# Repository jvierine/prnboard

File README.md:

# PRNboard

A standalone GNSS-timed PRN ionosonde exciter, intended to replace the transmit USRP and `tx_uhd.py` in [ionosonde](https://github.com/jvierine/ionosonde).

- **0.5–30 MHz**, uploaded binary phase code, **10–1000 µs chips** (default **30 µs**).
- **Continuous phase-continuous LFM**, typically **100 or 500 kHz/s**, using the AD9954 hardware ramp engine.
- Up to **1000 frequencies in user-defined order**, timed sweeps or single-frequency operation.
- GNSS PPS and disciplined **10 MHz TCXO**. **No qualified timing/frequency lock → no transmission.**
- **Wi-Fi and USB** configuration; stored programs run without a computer or internet.
- SMA exciter output; optional **separate protected, cooled 10 W PA**, with harmonic filtering and final 50 MHz LPF.
- Future telemetry and seven independently coded exciter outputs.

**Target: $50–100 per assembled exciter board**, using common parts with sustainable sourcing. Antenna, enclosure, adapter, cables, tax, freight, engineering, and PA are excluded. Revision B components total about **$77**, using a conservative $45 DDS allowance. Allow roughly **$95–115 assembled** in small batches; this is an estimate, not a fabrication quote.

**Current draft:** RP2040 timing/USB controller, ESP32-S3 Wi-Fi, AD9954 DDS (200 MHz, internal ×20 PLL), and stocked MAX-M10S GNSS. PRN and LFM register-level reference simulations pass; physical hardware remains untested. Any suitable dual-frequency raw-data receiver may replace the single-frequency fallback when availability and cost allow; TEC is optional.

**Status:** editable KiCad circuit and **unrouted placement study**, plus a tested host program compiler and end-to-end reference simulation. **Not ready to order.** Routing, firmware, sourcing and RF/timing validation remain. No fabrication order has been placed.

Current 95 × 85 mm placement draft, top view. Copper routing is unfinished; the 10 W PA is separate.

[End-to-end simulation and results](docs/end-to-end.md) · [Revision B and remaining work](docs/revision-b.md) · [LFM results](docs/lfm.md) · [Sourcing](docs/sourcing.md) · [Requirements](docs/requirements.md)

Open `hardware/prnboard.kicad_pro` in KiCad 10.

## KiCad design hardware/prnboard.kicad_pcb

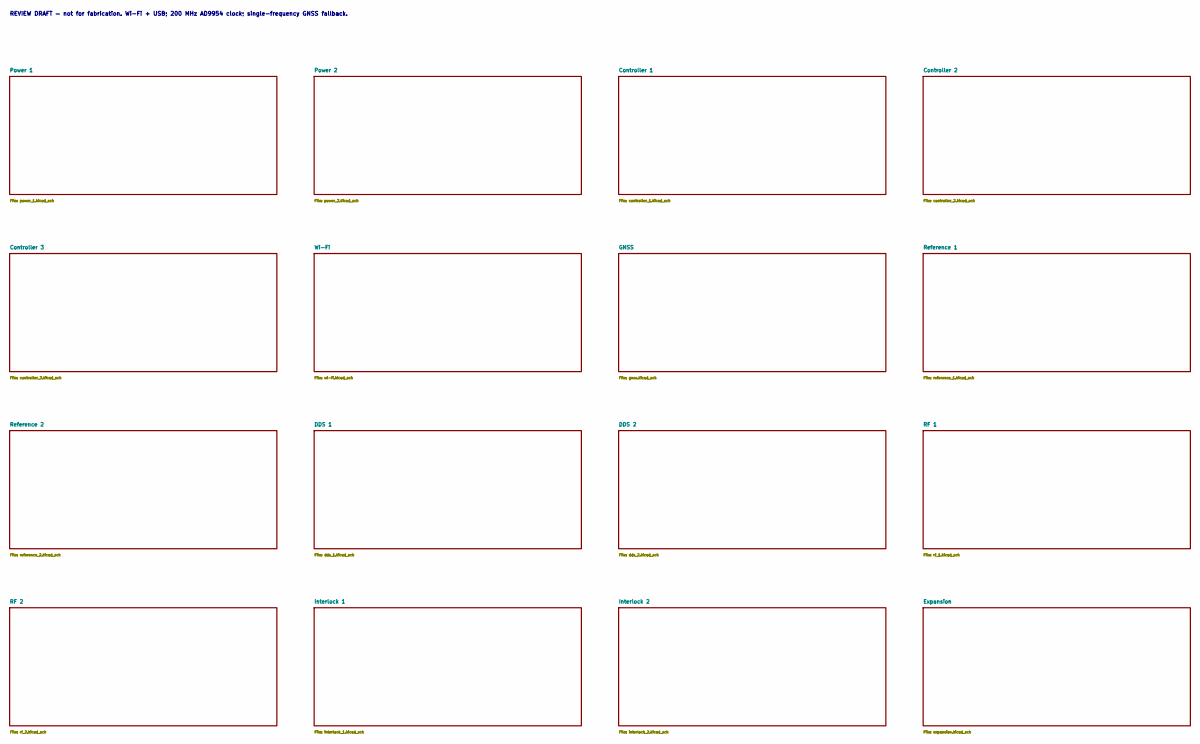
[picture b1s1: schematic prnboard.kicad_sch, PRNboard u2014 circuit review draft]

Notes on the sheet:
REVIEW DRAFT — not for fabrication. Wi-Fi + USB; 200 MHz AD9954 clock; single-frequency GNSS fallback.

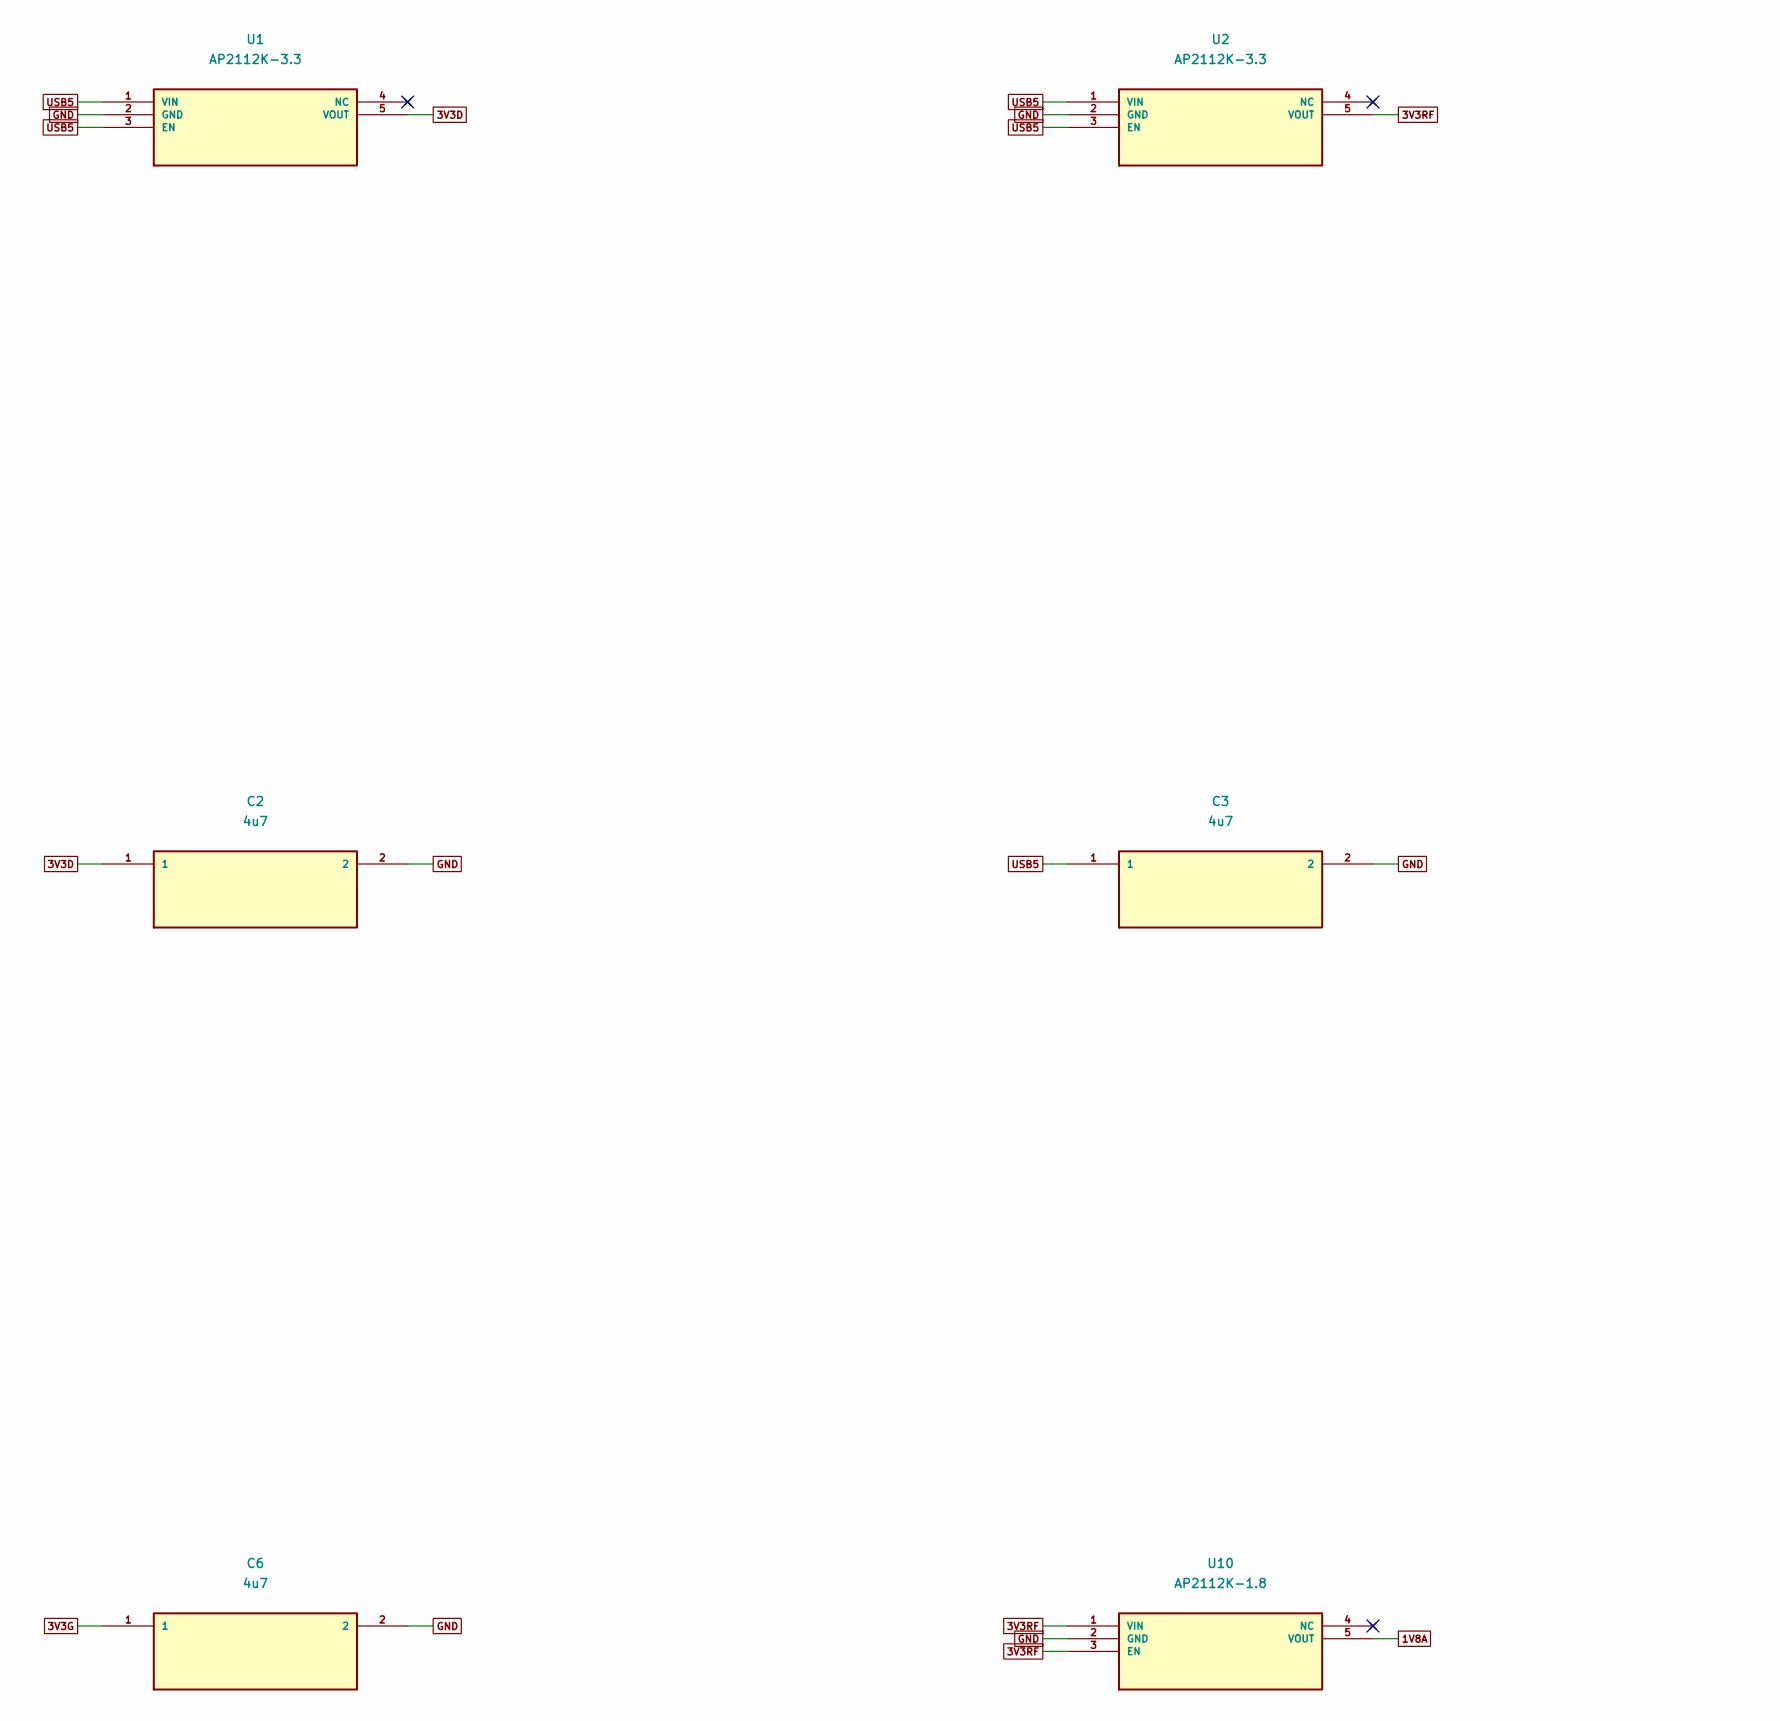
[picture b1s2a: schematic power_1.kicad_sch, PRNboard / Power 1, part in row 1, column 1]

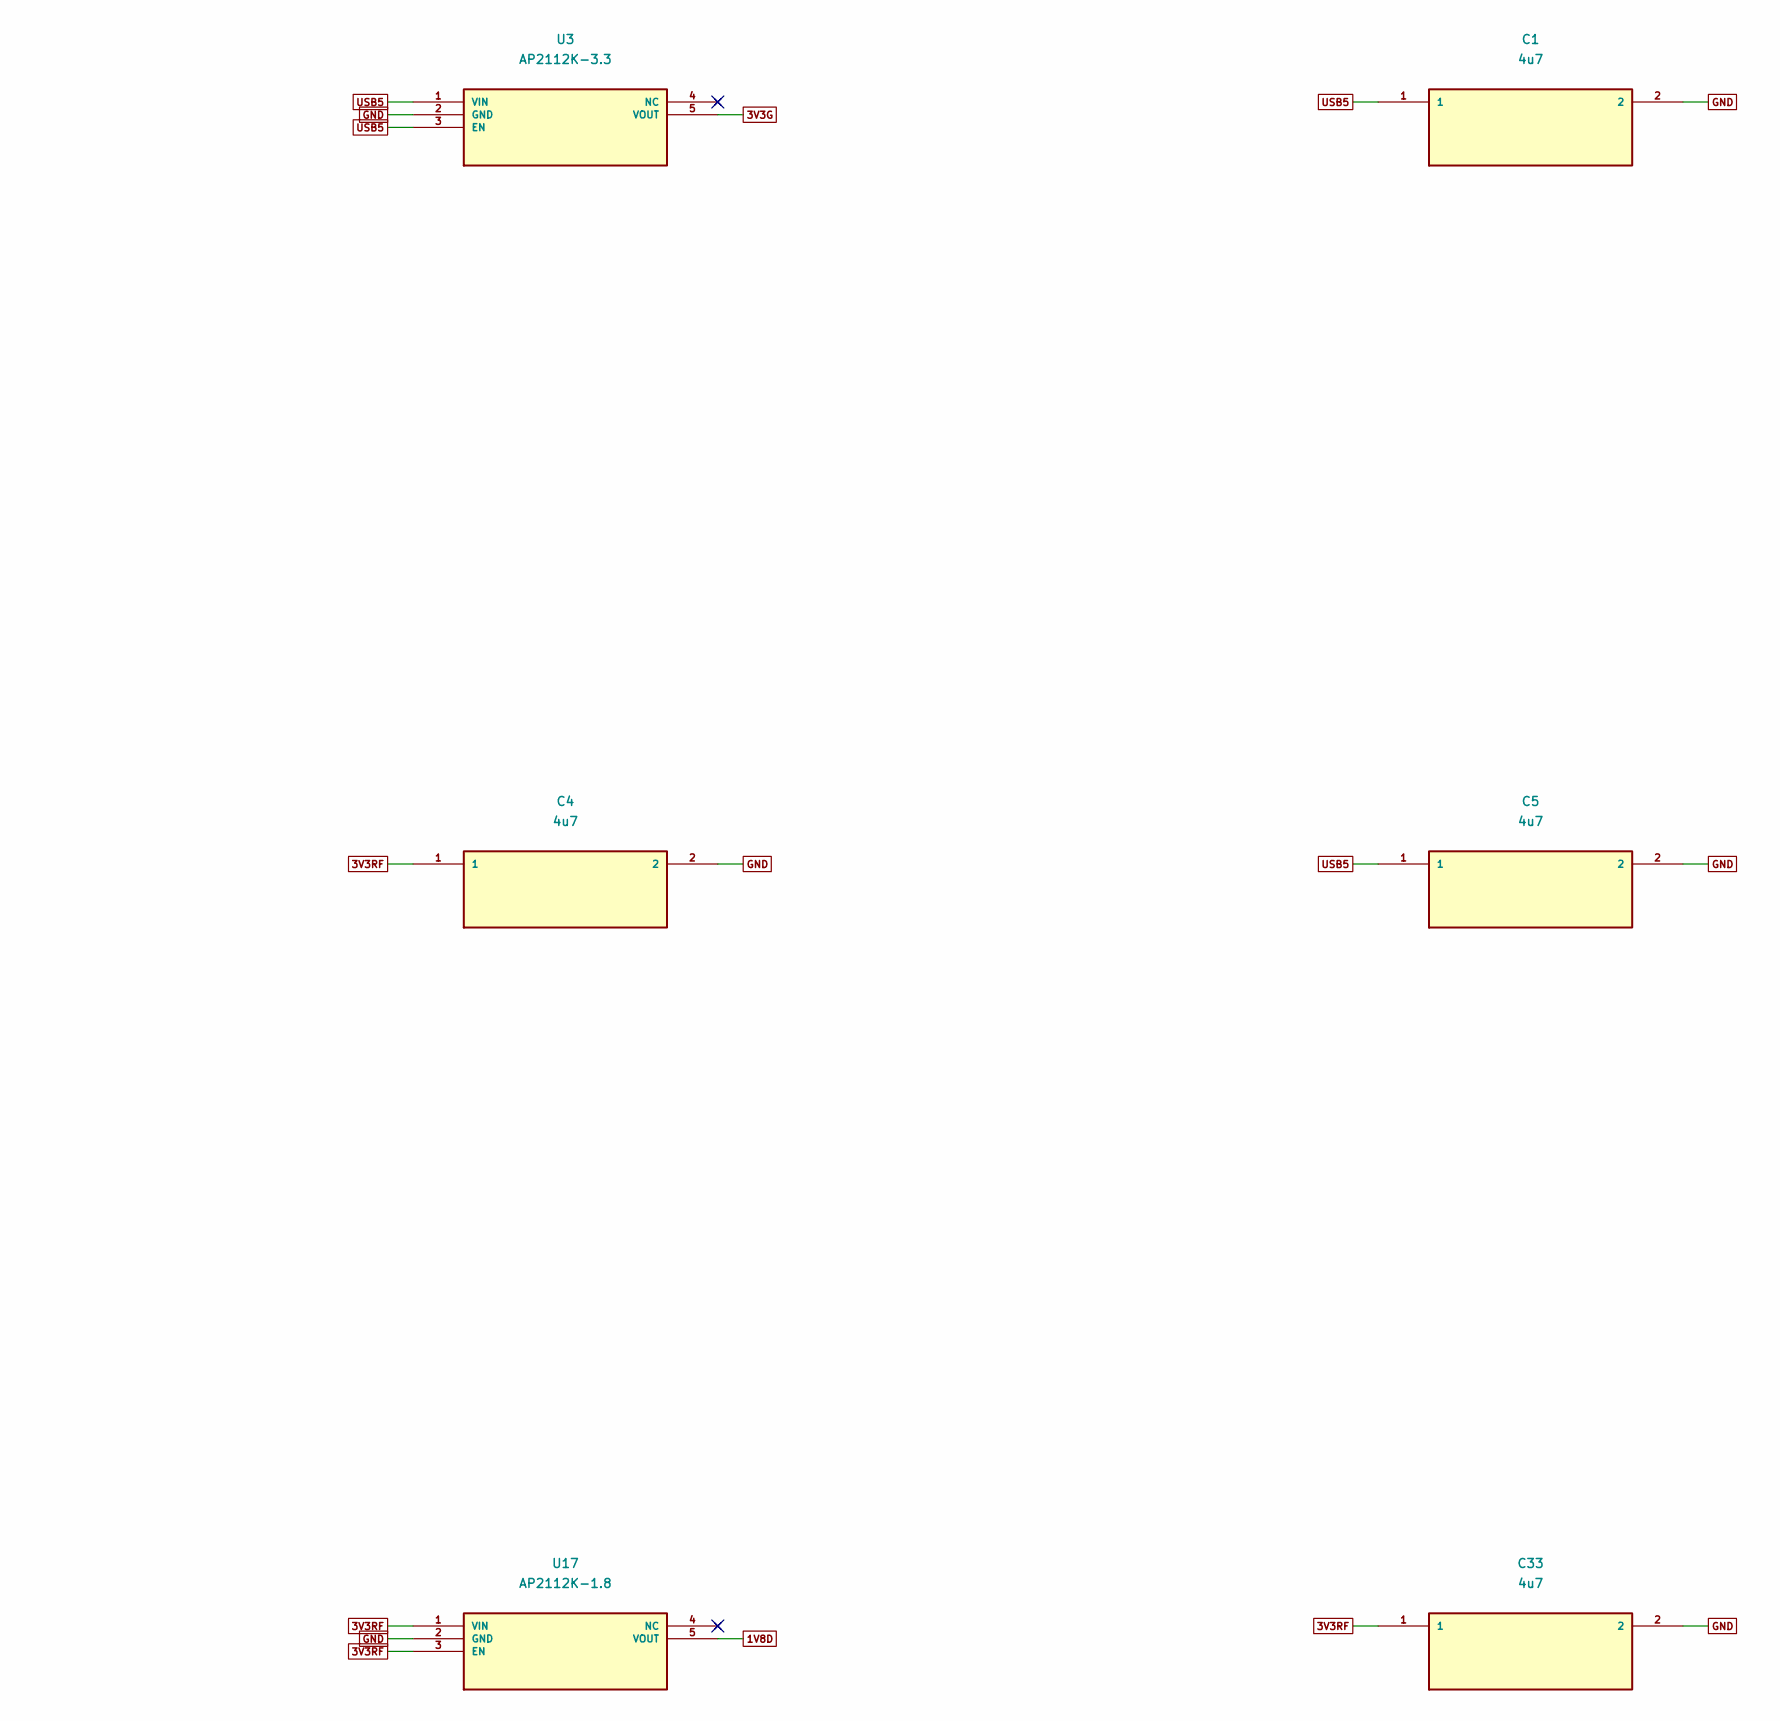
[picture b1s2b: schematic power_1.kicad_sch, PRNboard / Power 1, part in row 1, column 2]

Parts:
C1: 4u7; C1; MPN SELECT_IN_BOM
C2: 4u7; C2; MPN SELECT_IN_BOM
C3: 4u7; C3; MPN SELECT_IN_BOM
C4: 4u7; C4; MPN SELECT_IN_BOM
C5: 4u7; C5; MPN SELECT_IN_BOM
C6: 4u7; C6; MPN SELECT_IN_BOM
C33: 4u7; C33; MPN SELECT_IN_BOM
U1: AP2112K-3.3; U1; MPN AP2112K-3.3TRG1; LCSC C51118
U2: AP2112K-3.3; U2; MPN AP2112K-3.3TRG1; LCSC C51118
U3: AP2112K-3.3; U3; MPN AP2112K-3.3TRG1; LCSC C51118
U10: AP2112K-1.8; U10; MPN AP2112K-1.8TRG1
U17: AP2112K-1.8; U17; MPN AP2112K-1.8TRG1

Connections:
1V8A: U10.5 (VOUT); also elsewhere on the board
1V8D: U17.5 (VOUT); also elsewhere on the board
3V3D: C2.1, U1.5 (VOUT); also elsewhere on the board
3V3G: C6.1, U3.5 (VOUT); also elsewhere on the board
3V3RF: C4.1, C33.1, U2.5 (VOUT), U10.1 (VIN), U10.3 (EN), U17.1 (VIN), U17.3 (EN); also elsewhere on the board
GND: C1.2, C2.2, C3.2, C4.2, C5.2, C6.2, C33.2, U1.2 (GND), U2.2 (GND), U3.2 (GND), U10.2 (GND), U17.2 (GND); also elsewhere on the board
USB5: C1.1, C3.1, C5.1, U1.1 (VIN), U1.3 (EN), U2.1 (VIN), U2.3 (EN), U3.1 (VIN), U3.3 (EN); also elsewhere on the board

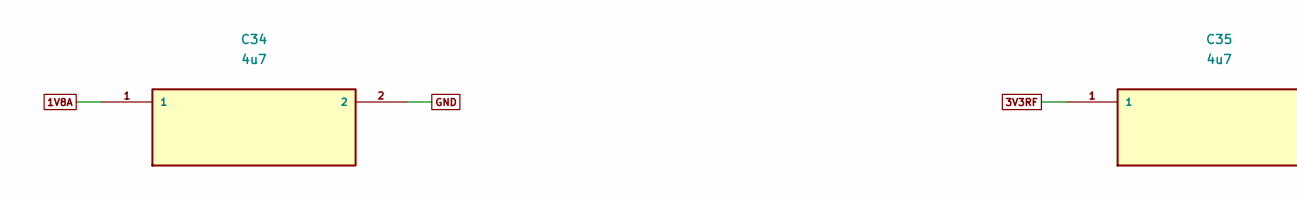
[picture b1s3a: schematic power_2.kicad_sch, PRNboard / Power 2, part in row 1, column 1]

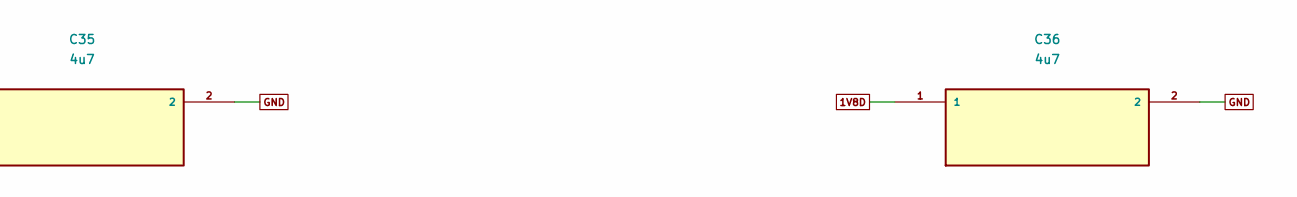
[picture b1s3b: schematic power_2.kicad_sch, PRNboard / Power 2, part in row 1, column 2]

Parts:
C34: 4u7; C34; MPN SELECT_IN_BOM
C35: 4u7; C35; MPN SELECT_IN_BOM
C36: 4u7; C36; MPN SELECT_IN_BOM

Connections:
1V8A: C34.1; also elsewhere on the board
1V8D: C36.1; also elsewhere on the board
3V3RF: C35.1; also elsewhere on the board
GND: C34.2, C35.2, C36.2; also elsewhere on the board

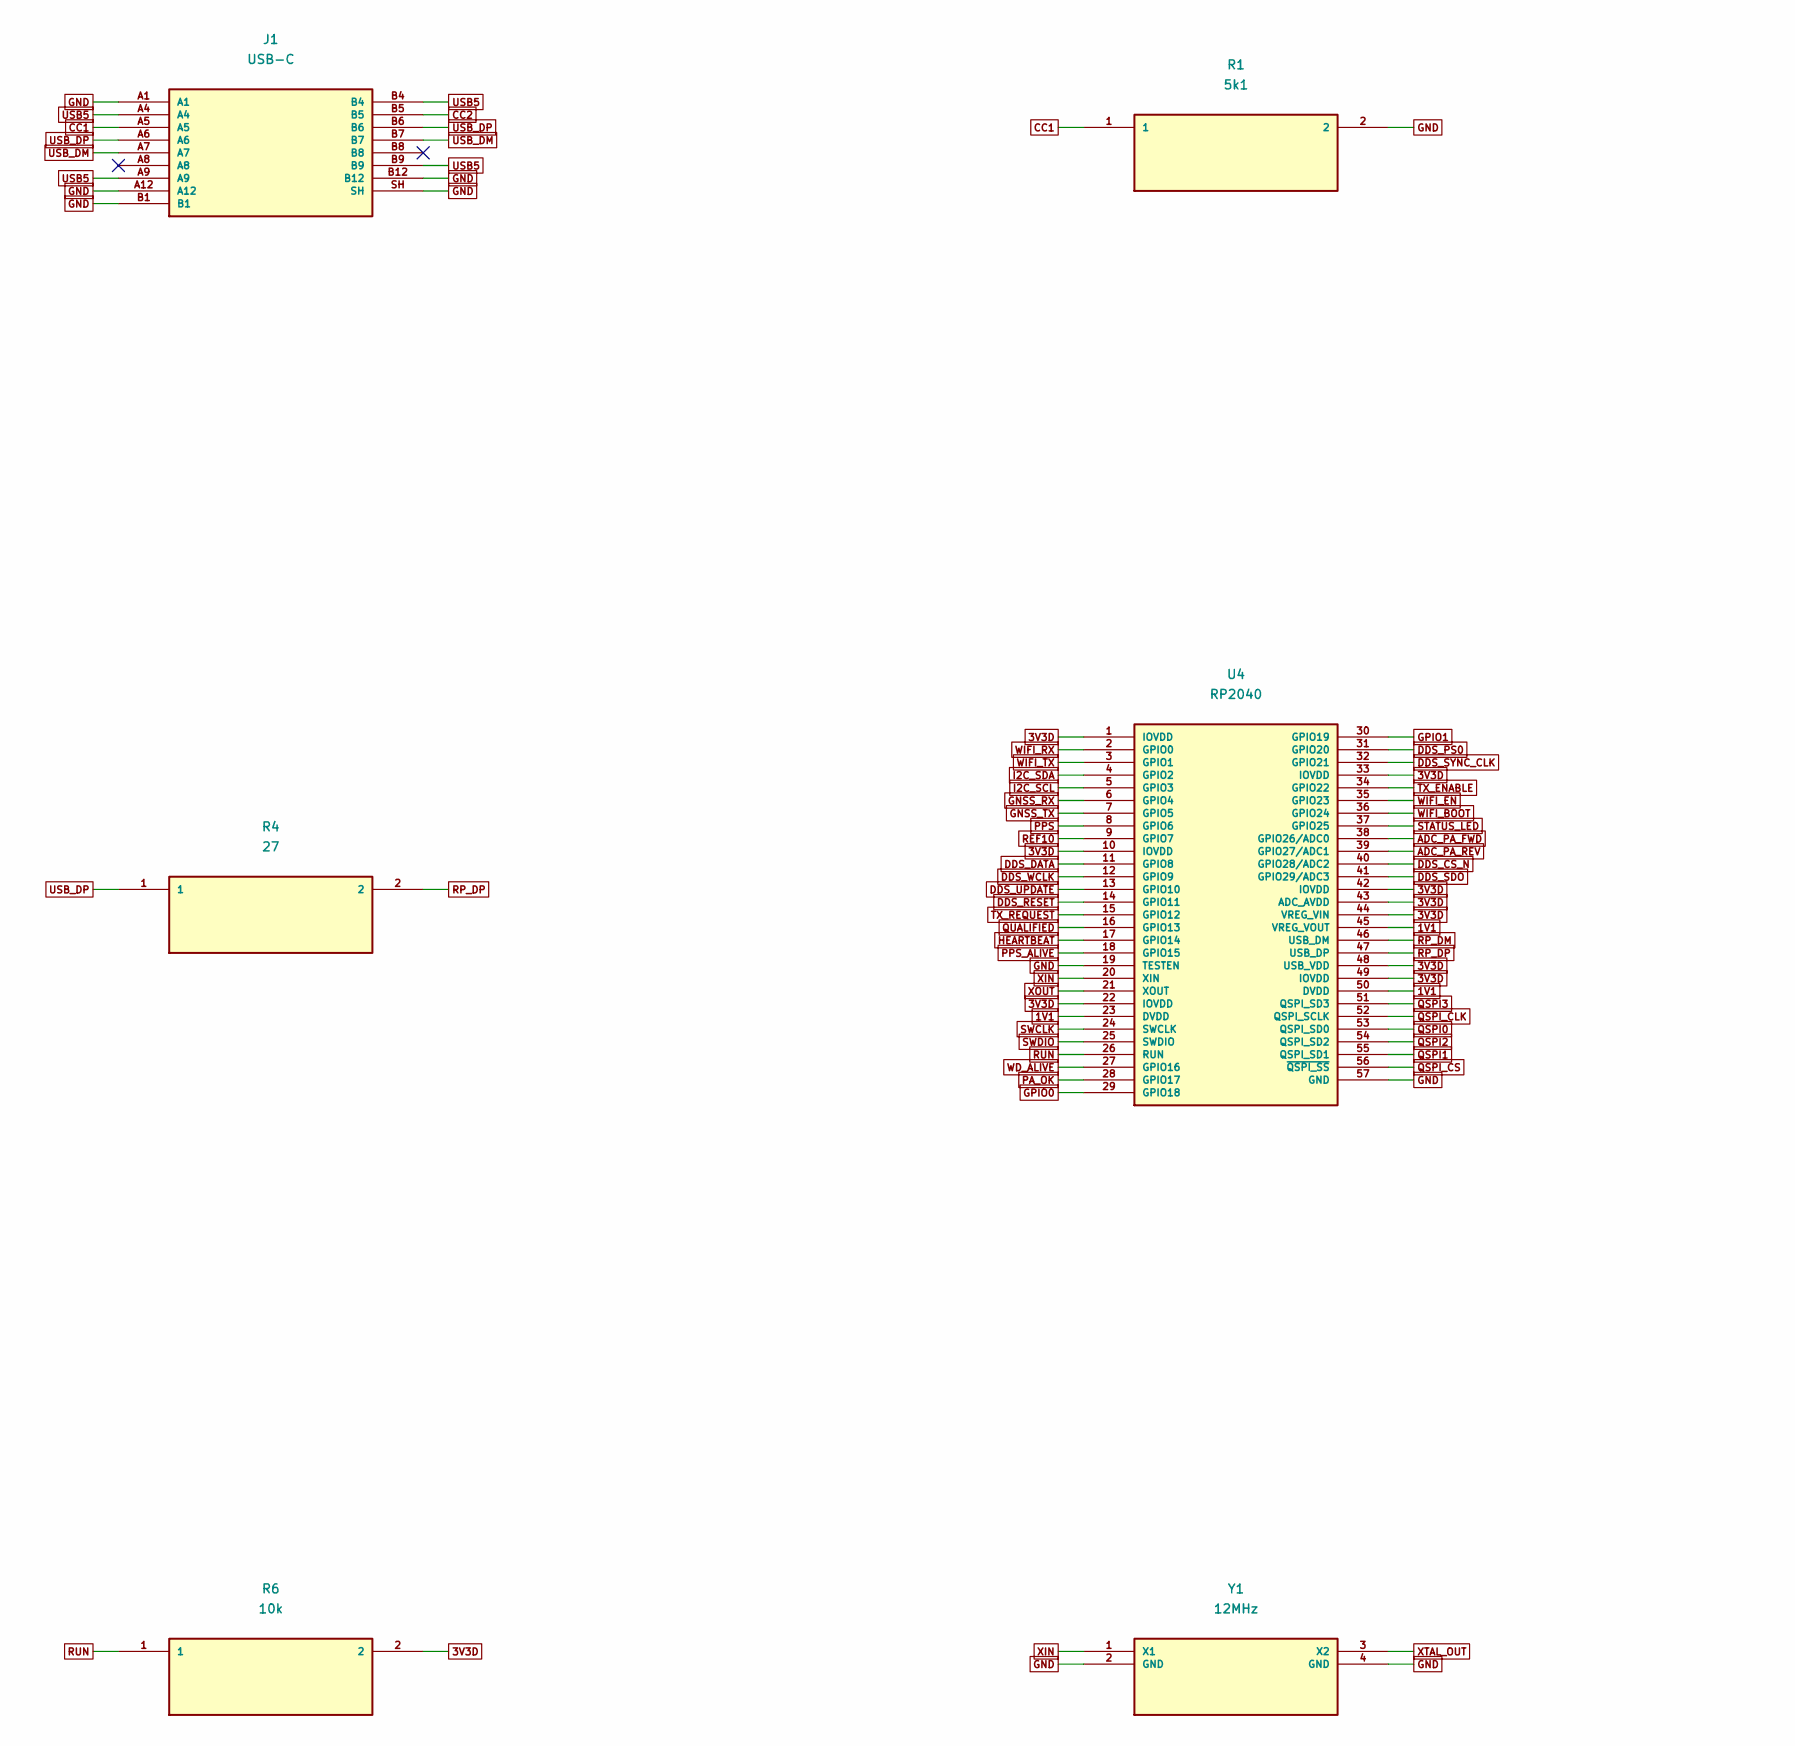
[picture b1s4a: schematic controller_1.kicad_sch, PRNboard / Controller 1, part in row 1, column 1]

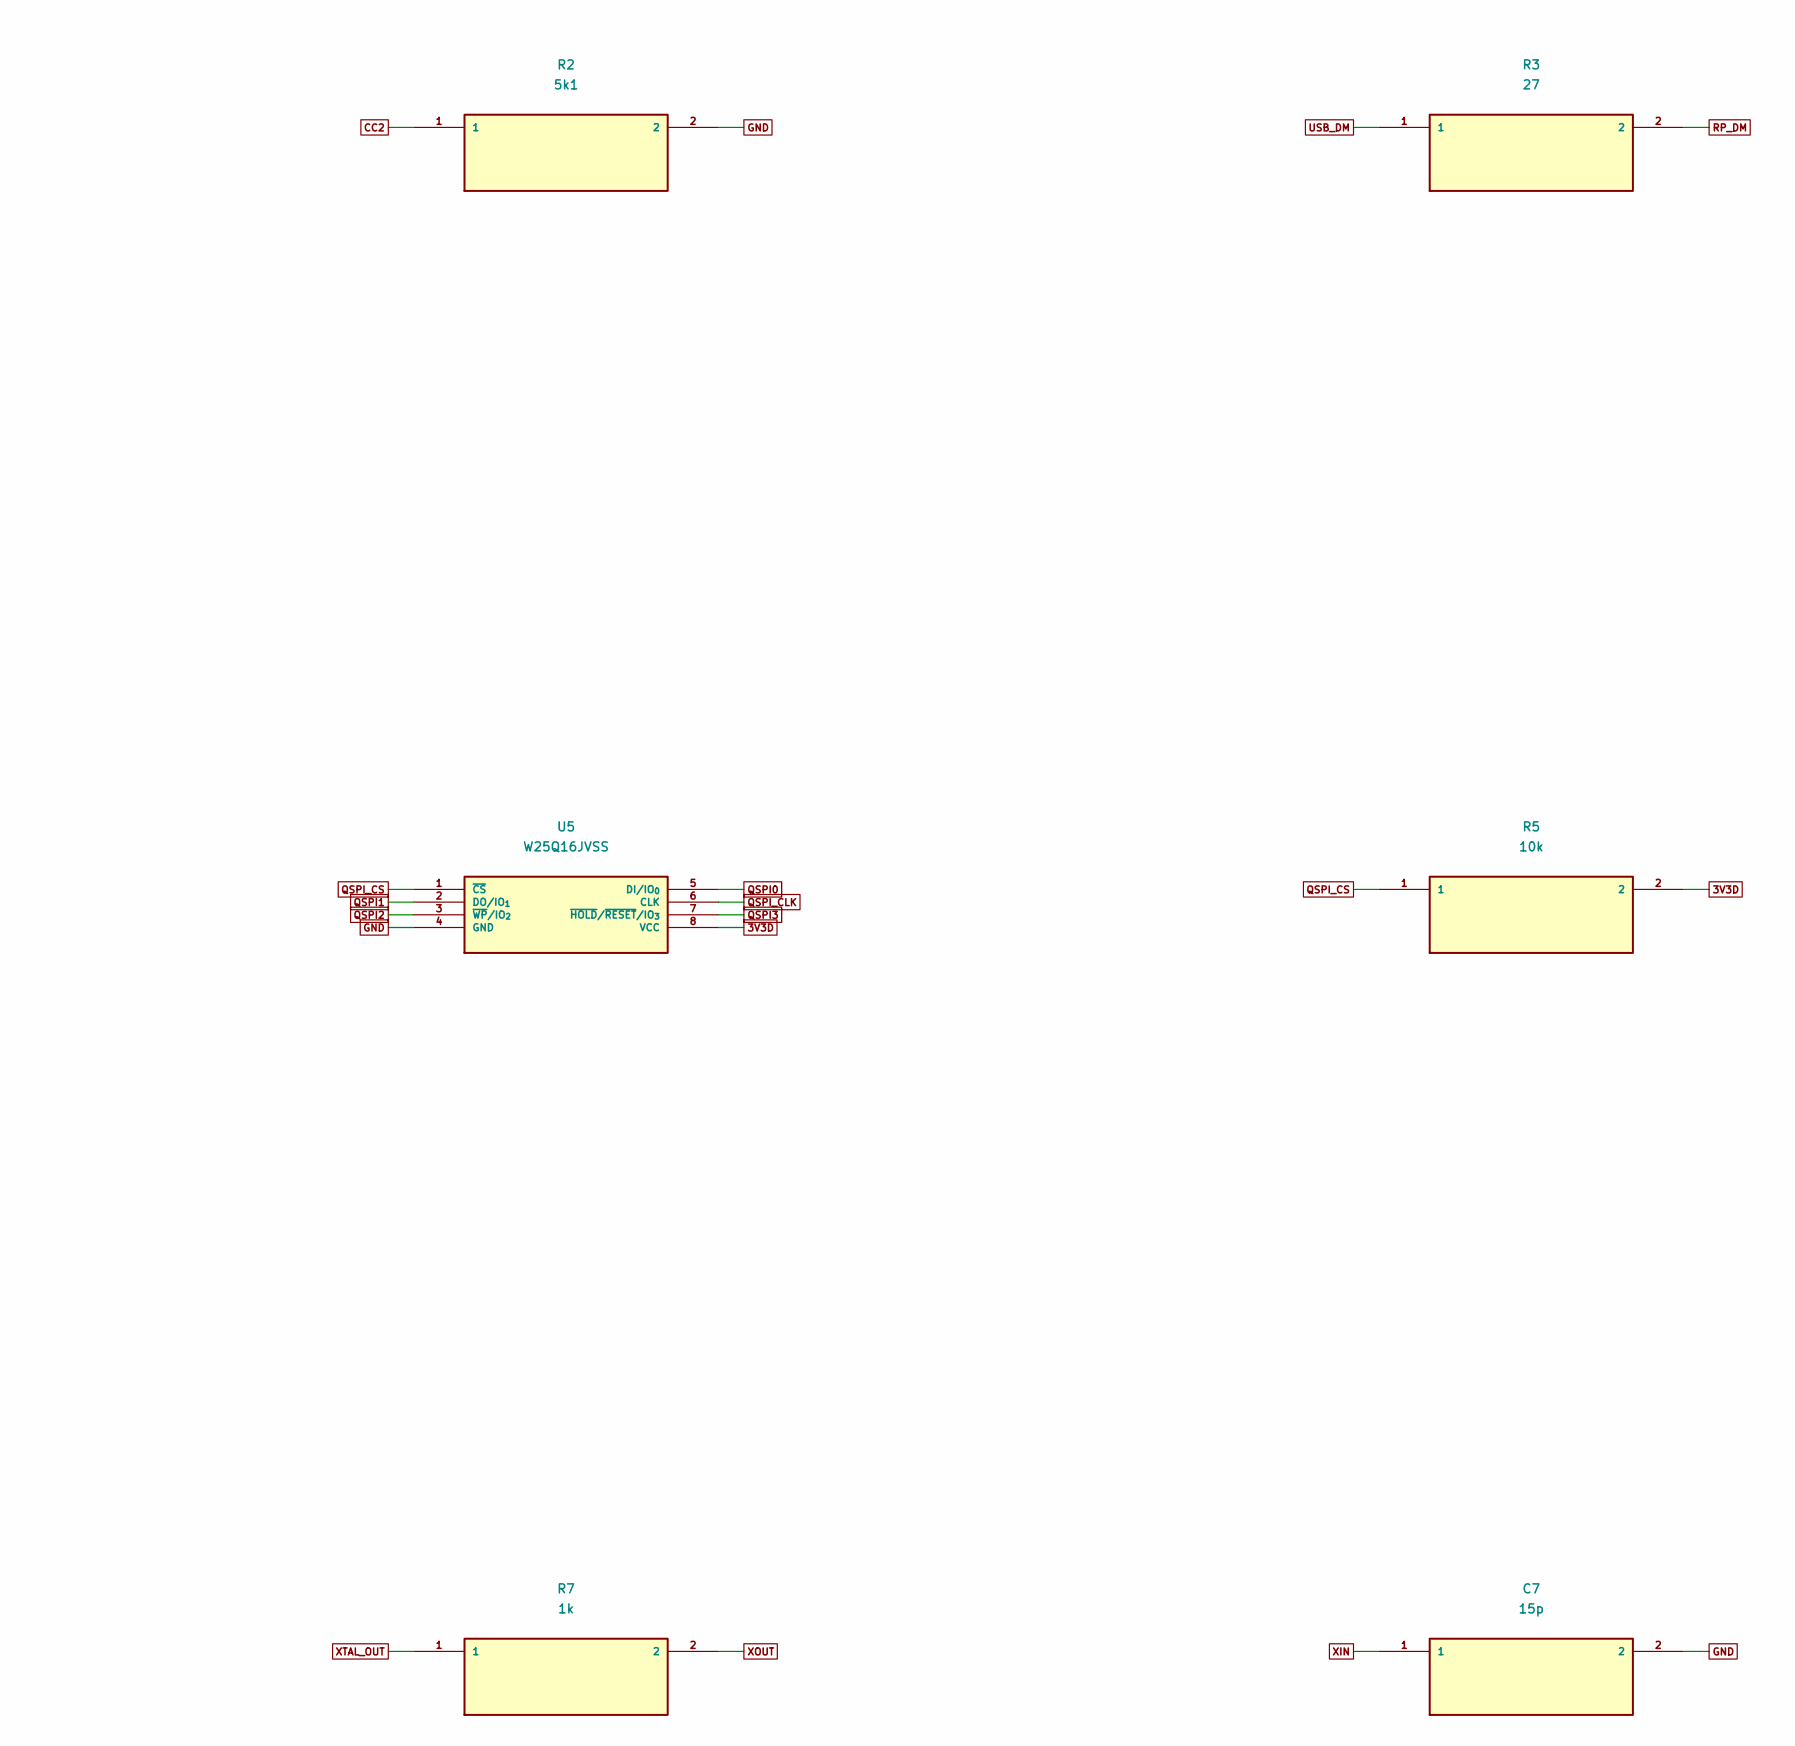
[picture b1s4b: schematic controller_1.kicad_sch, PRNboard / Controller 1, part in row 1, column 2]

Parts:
C7: 15p; C7; MPN SELECT_IN_BOM
J1: USB-C; J1; MPN TYPE-C-31-M-12; LCSC C165948
R1: 5k1; R1; MPN SELECT_IN_BOM
R2: 5k1; R2; MPN SELECT_IN_BOM
R3: 27; R3; MPN SELECT_IN_BOM
R4: 27; R4; MPN SELECT_IN_BOM
R5: 10k; R5; MPN SELECT_IN_BOM
R6: 10k; R6; MPN SELECT_IN_BOM
R7: 1k; R7; MPN SELECT_IN_BOM
U4: RP2040; U4; MPN RP2040; LCSC C2040
U5: W25Q16JVSS; U5; MPN W25Q16JVSS
Y1: 12MHz; Y1; MPN ABM8-272-T3

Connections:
1V1: U4.23 (DVDD), U4.45 (VREG_VOUT), U4.50 (DVDD); also elsewhere on the board
3V3D: R5.2, R6.2, U4.1 (IOVDD), U4.10 (IOVDD), U4.22 (IOVDD), U4.33 (IOVDD), U4.42 (IOVDD), U4.43 (ADC_AVDD), U4.44 (VREG_VIN), U4.48 (USB_VDD), U4.49 (IOVDD), U5.8 (VCC); also elsewhere on the board
ADC_PA_FWD: U4.38 (GPIO26/ADC0); also elsewhere on the board
ADC_PA_REV: U4.39 (GPIO27/ADC1); also elsewhere on the board
CC1: J1.A5, R1.1
CC2: J1.B5, R2.1
DDS_CS_N: U4.40 (GPIO28/ADC2); also elsewhere on the board
DDS_DATA: U4.11 (GPIO8); also elsewhere on the board
DDS_PS0: U4.31 (GPIO20); also elsewhere on the board
DDS_RESET: U4.14 (GPIO11); also elsewhere on the board
DDS_SDO: U4.41 (GPIO29/ADC3); also elsewhere on the board
DDS_SYNC_CLK: U4.32 (GPIO21); also elsewhere on the board
DDS_UPDATE: U4.13 (GPIO10); also elsewhere on the board
DDS_WCLK: U4.12 (GPIO9); also elsewhere on the board
GND: C7.2, J1.A1, J1.A12, J1.B1, J1.B12, J1.SH, R1.2, R2.2, U4.19 (TESTEN), U4.57 (GND), U5.4 (GND), Y1.2 (GND), Y1.4 (GND); also elsewhere on the board
GNSS_RX: U4.6 (GPIO4); also elsewhere on the board
GNSS_TX: U4.7 (GPIO5); also elsewhere on the board
GPIO0: U4.29 (GPIO18); also elsewhere on the board
GPIO1: U4.30 (GPIO19); also elsewhere on the board
HEARTBEAT: U4.17 (GPIO14); also elsewhere on the board
I2C_SCL: U4.5 (GPIO3); also elsewhere on the board
I2C_SDA: U4.4 (GPIO2); also elsewhere on the board
PA_OK: U4.28 (GPIO17); also elsewhere on the board
PPS: U4.8 (GPIO6); also elsewhere on the board
PPS_ALIVE: U4.18 (GPIO15); also elsewhere on the board
QSPI0: U4.53 (QSPI_SD0), U5.5 (DI/IO_{0})
QSPI1: U4.55 (QSPI_SD1), U5.2 (DO/IO_{1})
QSPI2: U4.54 (QSPI_SD2), U5.3 (~WP/IO_{2})
QSPI3: U4.51 (QSPI_SD3), U5.7 (~HOLD/~RESET/IO_{3})
QSPI_CLK: U4.52 (QSPI_SCLK), U5.6 (CLK)
QSPI_CS: R5.1, U4.56 (~QSPI_SS), U5.1 (~CS); also elsewhere on the board
QUALIFIED: U4.16 (GPIO13); also elsewhere on the board
REF10: U4.9 (GPIO7); also elsewhere on the board
RP_DM: R3.2, U4.46 (USB_DM)
RP_DP: R4.2, U4.47 (USB_DP)
RUN: R6.1, U4.26 (RUN); also elsewhere on the board
STATUS_LED: U4.37 (GPIO25); also elsewhere on the board
SWCLK: U4.24 (SWCLK); also elsewhere on the board
SWDIO: U4.25 (SWDIO); also elsewhere on the board
TX_ENABLE: U4.34 (GPIO22); also elsewhere on the board
TX_REQUEST: U4.15 (GPIO12); also elsewhere on the board
USB5: J1.A4, J1.A9, J1.B4, J1.B9; also elsewhere on the board
USB_DM: J1.A7, J1.B7, R3.1; also elsewhere on the board
USB_DP: J1.A6, J1.B6, R4.1; also elsewhere on the board
WD_ALIVE: U4.27 (GPIO16); also elsewhere on the board
WIFI_BOOT: U4.36 (GPIO24); also elsewhere on the board
WIFI_EN: U4.35 (GPIO23); also elsewhere on the board
WIFI_RX: U4.2 (GPIO0); also elsewhere on the board
WIFI_TX: U4.3 (GPIO1); also elsewhere on the board
XIN: C7.1, U4.20 (XIN), Y1.1 (X1)
XOUT: R7.2, U4.21 (XOUT)
XTAL_OUT: R7.1, Y1.3 (X2); also elsewhere on the board

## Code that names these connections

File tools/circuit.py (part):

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def cap(ref,net,x,y,section='Power',value='100n'):return passive(ref,value,net,'GND',x,y,section,'C')
# Regulator blocks: ESP radio current peaks isolated from GNSS/clock/DDS rails.
for ref,rail,x,y,enable in [('U1','3V3D',18,22,'USB5'),('U2','3V3RF',64,24,'USB5'),('U3','3V3G',78,25,'USB5')]:
 add(ref,'AP2112K-3.3', 'Power',x,y,pins=['VIN','GND','EN','NC','VOUT'],nets={'1':'USB5','2':'GND','3':enable,'5':rail},fp='Package_TO_SOT_SMD:SOT-23-5',mpn='AP2112K-3.3TRG1',cost=.18,lcsc='C51118')
for i,(rail,x,y) in enumerate([('USB5',14,22),('3V3D',22,22),('USB5',60,24),('3V3RF',68,24),('USB5',74,25),('3V3G',82,25)],1):cap('C'+str(i),rail,x,y,value='4u7')
# USB-C receptacle, both CC pull-downs. Connector pad map must be confirmed with exact supplier drawing.
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add('U4','RP2040','Controller',28,34,'MCU_RaspberryPi','RP2040',rp,mpn='RP2040',cost=.9,lcsc='C2040')
add('U5','W25Q16JVSS','Controller',16,35,'Memory_Flash','W25Q16JVSS',{'1':'QSPI_CS','2':'QSPI1','3':'QSPI2','4':'GND','5':'QSPI0','6':'QSPI_CLK','7':'QSPI3','8':'3V3D'},cost=.35)
passive('R5','10k','QSPI_CS','3V3D',16,30,'Controller');passive('R6','10k','RUN','3V3D',25,24,'Controller')
add('Y1','12MHz','Controller',28,46,pins=['X1','GND','X2','GND'],nets={'1':'XIN','2':'GND','3':'XTAL_OUT','4':'GND'},fp='Crystal:Crystal_SMD_3225-4Pin_3.2x2.5mm',mpn='ABM8-272-T3',cost=.2)
passive('R7','1k','XTAL_OUT','XOUT',32,46,'Controller');cap('C7','XIN',24,46,'Controller','15p');cap('C8','XTAL_OUT',28,50,'Controller','15p')
for i,(rail,x,y) in enumerate([('3V3D',25,29),('3V3D',31,29),('3V3D',33,34),('3V3D',31,39),('3V3D',25,39),('1V1',23,34),('1V1',29,41),('3V3D',16,39)],9):cap('C'+str(i),rail,x,y,'Controller')
cap('C17','1V1',23,38,'Controller','1u');cap('C18','RUN',25,21,'Controller')
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g={'1':'GND','2':'GNSS_TX','3':'GNSS_RX','4':'PPS','6':'3V3G','7':'3V3G','8':'3V3G','10':'GND','11':'GNSS_RF','12':'GND'}
add('U7','MAX-M10S-00B','GNSS',78,12,'RF_GPS','MAX-M10S',g,mpn='MAX-M10S-00B',cost=10.5062,lcsc='C4153167',note='VIO_SEL and TIMEPULSE/SAFEBOOT left unpulled. Single-frequency: no dual-frequency TEC.')
cap('C22','3V3G',70,12,'GNSS');cap('C23','3V3G',70,16,'GNSS','4u7')
add('J2','GNSS ANT','GNSS',88,12,pins=['RF','GND'],nets={'1':'ANT_RF','2':'GND'},fp='Connector_Coaxial:SMA_Amphenol_132134_Vertical',mpn='132134',cost=1.5,note='Candidate vertical SMA; supplier/price not frozen.')
passive('C24','100p','ANT_RF','GNSS_RF',83,12,'GNSS','C');passive('L1','27n','ANT_BIAS','ANT_RF',86,18,'GNSS','L',.12);passive('R10','100','3V3G','ANT_BIAS',82,21,'GNSS',cost=.03);cap('C25','ANT_BIAS',86,23,'GNSS','1n')
# Antenna supply current limited by 100ohm/0.25W resistor: check antenna headroom.
parts[-2]['note']='Use >=0.25W 0805 and check active-antenna voltage/current; provisional bias network.'
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passive('R11','1k','DAC','DAC_FILTER',50,38,'Reference');passive('R12','1k','DAC_FILTER','VCTRL',55,38,'Reference');cap('C26','DAC_FILTER',50,42,'Reference','4u7');cap('C27','VCTRL',55,42,'Reference','4u7')
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cap('C28','3V3RF',61,34,'Reference');passive('C29','1n','OSC_SINE','SINE_AC',66,38,'Reference','C');passive('R13','10k','3V3RF','MID',66,32,'Reference');passive('R14','10k','MID','GND',70,32,'Reference');cap('C30','MID',70,35,'Reference','4u7');passive('R15','10k','MID','SINE_AC',70,39,'Reference')
add('U9','TLV3501AIDBVR','Reference',75,38,pins=['IN-','GND','IN+','VCC','OUT','SHDN'],nets={'1':'MID','2':'GND','3':'SINE_AC','4':'3V3RF','5':'REF10','6':'GND'},fp='Package_TO_SOT_SMD:SOT-23-6',cost=2.2)
cap('C31','3V3RF',77,34,'Reference');cap('C32','3V3RF',45,34,'Reference')
passive('R16','1k','I2C_SDA','3V3D',38,32,'Reference');passive('R17','1k','I2C_SCL','3V3D',38,35,'Reference')
# AD9954 uses its own x20 PLL: 10 MHz disciplined reference -> 200 MHz DDS.
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passive('R24','49R9','LP_OUT','1V8A',86,59,'RF');passive('C45','100n','LP_OUT','RF_IN_AC',87,63,'RF','C')
passive('R25','10k','RF_IN_AC','MID',87,67,'RF')
# SPDT mute before driver, mute selects DC bias. Exact switch truth table must be checked before release.
add('U12','TS5A3159DBVR','RF',81,70,'Analog_Switch','TS5A3159DBV',{'1':'RF_IN_AC','2':'GND','3':'AMP_IN','4':'MID','5':'3V3RF','6':'TX_ENABLE'},mpn='TS5A3159DBVR',cost=.5,note='Pin1 NO, pin3 COM, pin4 NC: high enables RF; low selects MID.')
add('U13','OPA356AIDBVR','RF',72,71,'Amplifier_Operational','OPA356xxDBV',{'1':'AMP_OUT','2':'GND','3':'AMP_IN','4':'AMP_FB','5':'3V3RF'},mpn='OPA356AIDBVR',cost=1.8)
passive('R26','300','AMP_OUT','AMP_FB',72,67,'RF');passive('R27','100','AMP_FB','MID',68,67,'RF');passive('R28','49R9','AMP_OUT','RF_SERIES',67,71,'RF');passive('C46','100n','RF_SERIES','RF_OUT',62,71,'RF','C')
cap('C47','3V3RF',75,75,'RF');cap('C48','3V3RF',83,74,'RF')
add('J3','EXCITER OUT','RF',55,76,pins=['RF','GND'],nets={'1':'RF_OUT','2':'GND'},fp='Connector_Coaxial:SMA_Amphenol_132134_Vertical',mpn='132134',cost=1.5)
# Missing PPS and firmware heartbeat: independent retriggerable monostables.
wd={'1':'GND','2':'PPS','3':'RUN','4':None,'5':'WD_ALIVE','6':'WD_C','7':'WD_RC','8':'GND','9':'GND','10':'HEARTBEAT','11':'RUN','12':None,'13':'PPS_ALIVE','14':'PPS_C','15':'PPS_RC','16':'3V3D'}
add('U14','74HC123D','Interlock',28,63,'74xx','74HC123',wd,fp='Package_SO:SOIC-16_3.9x9.9mm_P1.27mm',mpn='74HC123D,653',cost=.3)
passive('R29','1M','3V3D','PPS_RC',22,56,'Interlock');passive('C49','4u7','PPS_C','PPS_RC',25,56,'Interlock','C')
passive('R30','100k','3V3D','WD_RC',22,70,'Interlock');passive('C50','1u','WD_C','WD_RC',25,70,'Interlock','C');cap('C51','3V3D',32,57,'Interlock')
add('U15','74LVC2G08','Interlock',39,63,'74xGxx','74LVC2G08',{'1':'PPS_ALIVE','2':'WD_ALIVE','7':'CLOCK_ALIVE','3':'ARMED','5':'QUALIFIED','6':'TX_REQUEST','4':'GND','8':'3V3D'},fp='Package_SO:VSSOP-8_2.3x2mm_P0.5mm',mpn='74LVC2G08DC,125',cost=.15)
add('U16','SN74LVC1G08DBVR','Interlock',44,69,pins=['A','B','GND','Y','VCC'],nets={'1':'CLOCK_ALIVE','2':'ARMED','3':'GND','4':'TX_ENABLE','5':'3V3D'},fp='Package_TO_SOT_SMD:SOT-23-5',cost=.12)
for i,(net,x,y) in enumerate([('TX_REQUEST',35,56),('QUALIFIED',38,56),('HEARTBEAT',41,56),('TX_ENABLE',47,69)],31):passive('R'+str(i),'10k',net,'GND',x,y,'Interlock')
cap('C52','3V3D',39,59,'Interlock');cap('C53','3V3D',44,65,'Interlock')
# Headers: no PA supply or 10W circuitry on this board.
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passive('R35','10k','PA_OK','GND',16,67,'Interlock')
# Status LED and debug boot contacts are not relied upon for safety.
add('D1','GREEN','Controller',34,22,pins=['K','A'],nets={'1':'GND','2':'LED_A'},fp='LED_SMD:LED_0603_1608Metric',cost=.03);passive('R36','1k','STATUS_LED','LED_A',34,25,'Controller')
for ref,net,x,y in [('SW1','RUN',7,28),('SW2','QSPI_CS',7,22)]:
 add(ref,'RESET' if ref=='SW1' else 'BOOT','Controller',x,y,pins=['1','2'],nets={'1':net,'2':'GND'},fp='Button_Switch_SMD:SW_SPST_TL3342',mpn='TL3342F160QG',cost=.1)
# ESD protection and isolatable onboard GNSS outputs for a later TEC receiver.
add('D2','USBLC6-2SC6','Controller',16,11,pins=['IO1','GND','IO2','IO2','VBUS','IO1'],nets={'1':'USB_DM','2':'GND','3':'USB_DP','4':'USB_DP','5':'USB5','6':'USB_DM'},fp='Package_TO_SOT_SMD:SOT-23-6',cost=.2,lcsc='C7519')
next(p for p in parts if p['ref']=='U7')['pins'][1]['net']='GNSS_TX_ONBOARD'
next(p for p in parts if p['ref']=='U7')['pins'][3]['net']='PPS_ONBOARD'
passive('R37','0','GNSS_TX_ONBOARD','GNSS_TX',72,20,'GNSS')
passive('R38','0','PPS_ONBOARD','PPS',75,20,'GNSS')
for p in parts:
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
